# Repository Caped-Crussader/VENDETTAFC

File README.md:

# VENDETTA FPV Stack

> A fully open-source, custom-designed 4-in-1 ESC and F7 Flight Controller stack for FPV multirotors, designed from scratch in KiCad.

---

## Overview

The VENDETTA stack consists of two boards designed to work together as a matched pair, built around modern components and open firmware with no proprietary dependencies.

| Board | Folder | Status |
|---|---|---|
| VENDETTA ESC (VESC) | `/VESC` | Schematic complete, layout WIP |
| VENDETTA FC (VFC) | `/VFC` | Schematic complete, layout WIP |

---

## VENDETTA ESC (VESC)

A 30×30mm 4-in-1 ESC (25A x 4) designed for 3–6S FPV multirotors.

> Note: 6 Layer Board, GND (plane 2 and 5) plane photos not included.

### Specifications

| Parameter | Value |
|---|---|
| MCU | Artery AT32F421GBU7 |
| Gate Driver | NSG2065Q |
| MOSFETs | SP40N03GNJ (×6 per channel, 24 total) |
| Continuous current | 25A per channel |
| Burst current | 30A per channel |
| Input voltage | 3–6S LiPo (12.6V–25.2V) |
| Motor outputs | 4× 3-phase BLDC |
| Firmware | AM32 |
| Protocols | DShot150 / DShot300 / DShot600 |
| Telemetry | Bidirectional DShot (RPM) |
| Current sensing | INA185 + 0.5mΩ Kelvin shunt |
| TVS protection | SMBJ30A |
| Bulk capacitance | 320µF (32× 10µF MLCC) |
| BEC (8V) | MP9943GQ-Z |
| BEC (3.3V) | TLV76733 |
| Mounting | 30×30mm M3 |
| Connector | JST SH 1.0mm 8-pin (SM08B-SRSS-TB) |

### ESC Block Diagram

```
LiPo ──→ TVS + Bulk Caps ──→ 4× Half-Bridge (NSG2065Q + SP40N03GNJ)
                           ──→ 8V BEC ──→ Gate Driver VCC
                           ──→ Shunt (0.5mΩ Kelvin) ──→ INA185 ──→ AT32F421
AT32F421 ──→ DShot (from FC) ──→ PWM generation ──→ NSG2065Q ──→ Motors
```

---

## VENDETTA FC (VFC)

A 30×30mm F7 Flight Controller targeting feature parity with commercial boards like the SpeedyBee F7 V3, with improvements in IMU performance and power isolation.

> Note: 6 Layer Board, GND (plane 2 and 5) plane photos not included.

### Specifications

| Parameter | Value |
|---|---|
| MCU | STM32F722RETx (216MHz Cortex-M4) |
| IMU | ICM-42688-P (32kHz gyro, SPI) |
| Barometer | BMP388 (I2C) |
| Blackbox | W25N04KVZEIR (512MB NAND Flash, SPI) |
| Wireless | ESP32-C3 (WiFi + BT via UART1) |
| OSD | None (digital OSD via MSP DisplayPort) |
| Firmware | Betaflight |
| Motor outputs | 4× DShot (TIM2 CH1–CH4, PA0–PA3) |
| UARTs | 6× (UART3 OSD, UART4 DJI RX, UART5 ELRS, UART6 GPS, UART7 spare) |
| I2C | 1× (GPS compass) |
| USB | USB-C (USB 2.0 FS) |
| BEC (9V/2A) | MP9943GQ-Z |
| BEC (5V/3A) | MP9943GQ-Z |
| LDO Digital (3.3V/1A) | AP7361C |
| LDO Analog (3.3V/700mA) | NCP167AMX330 |
| Blackbox | 512MB onboard flash |
| DJI support | Air Unit / O3 via UART3+UART4 |
| GPS | UART7 + I2C (compass) |
| Receiver | UART5 (ELRS/CRSF/SBUS) |
| LED outputs | 4× |
| Buzzer | MOSFET driven |
| Mounting | 30×30mm M3 |

### FC Block Diagram

```
                    ┌─────────────────────────────┐
LiPo (via ESC) ────→│ 9V BEC → 5V BEC → 3.3V x2  │
                    │                             │
                    │  STM32F722 ←─SPI─→ ICM-42688-P (IMU)
                    │             ←─SPI─→ W25N04KV (Flash)
                    │             ←─UART1─→ ESP32-C3 (WiFi/BT)
                    │             ←─I2C─→ BMP388 (Baro)
                    │             ←─USB─→ USB-C
                    │             ──UART3/4──→ DJI Air Unit
                    │             ──UART5────→ Receiver (ELRS)
                    │             ──UART6────→ GPS
                    │             ──TIM2─────→ ESC DShot M1-M4
                    └─────────────────────────────┘
```

### Power Architecture

```
VBAT (from ESC 8-pin) ──→ 9V/2A (MP9943) ──→ DJI Air Unit
                                           ──→ 5V/3A (MP9943) ──→ JST 5V outputs
                                                               ──→ 3.3V Digital (AP7361C) ──→ STM32, ESP32, Flash
                                                               ──→ [Ferrite] ──→ 3.3V Analog (NCP167) ──→ IMU, Baro, VDDA
```

---

## Connector Pinout

### ESC → FC (JST SH 1.0mm 8-pin)

| Pin | Signal | Description |
|---|---|---|
| 1 | VBAT | Battery voltage |
| 2 | GND | Ground |
| 3 | M1 | Motor 1 DShot |
| 4 | M2 | Motor 2 DShot |
| 5 | M3 | Motor 3 DShot |
| 6 | M4 | Motor 4 DShot |
| 7 | CURR | Current sense (INA185 output) |
| 8 | TLM | ESC telemetry UART |

### FC Bottom Connectors (JST SH 1.0mm)

| Connector | Pins | Function |
|---|---|---|
| ESC | 8 | M1–M4, CURR, TLM, VBAT, GND |
| RECEIVER | 4 | +5V, GND, UART5_RX, UART5_TX |
| GPS | 6 | +5V, GND, UART6_TX, UART6_RX, SDA, SCL |
| DJI AIR UNIT | 6 | +9V, GND, UART3_TX, UART3_RX, UART4_RX, NC |
| UART5 | 4 | +5V, GND, TX, RX |
| LED 1–4 | 3 each | +5V, GND, Signal |
| BUZZER | 2 | +5V, Signal |

---

## Firmware (Not yet Completed)

### ESC — AM32

AM32 is the only supported firmware for the AT32F421 MCU.

Flash via DShot passthrough from Betaflight:
```
Betaflight Configurator → Motors → ESC Configuration → Flash All
```

Or via SWD using the exposed test pads (SWDIO/SWDCLK).

Recommended target: `AT32F421_VESC` — confirm correct pin mapping before flashing.

### FC — Betaflight

Target: `STM32F7X2` unified target or a custom target for this board.

Flash via USB DFU:
1. Hold BOOT button, plug USB-C
2. Open Betaflight Configurator → Firmware Flasher
3. Select STM32F7X2, flash

Or wirelessly via ESP32-C3 over WiFi through the SpeedyBee App.

---

## Repository Structure

```
VENDETTAFC/
├── VESC/
│   ├── VESC.kicad_pro
│   ├── VESC.kicad_sch
│   ├── ESC1.kicad_sch        # Per-channel ESC subsheet
│   └── ...
├── VFC/
│   ├── VENDETTAFC.kicad_pro
│   ├── VENDETTAFC.kicad_sch  # Top-level schematic
│   ├── interface.kicad_sch   # Connectors and I/O
│   ├── pwr.kicad_sch         # Power management
│   ├── sensor.kicad_sch      # IMU, baro, flash, ESP32
│   └── ...
└── README.md
```

---

## Design Files

Both boards are designed in **KiCad 10**. All schematic symbols and footprints use standard KiCad libraries plus LCSC-sourced footprints where needed.

To open:
```
KiCad 10 → Open Project → select .kicad_pro file
```

---

## Status

- [x] ESC schematic complete
- [x] FC schematic complete  
- [x] ESC PCB layout
- [x] FC PCB layout
- [x] Gerber generation
- [ ] First prototype order
- [ ] Firmware bringup
- [ ] Testing and validation

---

## License

Hardware design files are released under the **CERN Open Hardware Licence Version 2 - Strongly Reciprocal (CERN-OHL-S v2)**.

You are free to study, modify, distribute, and manufacture this hardware, provided derivatives are released under the same license with attribution.

---

## Author

Designed by **Caped-Crussader**

> Contributions, bug reports, and suggestions welcome via Issues.

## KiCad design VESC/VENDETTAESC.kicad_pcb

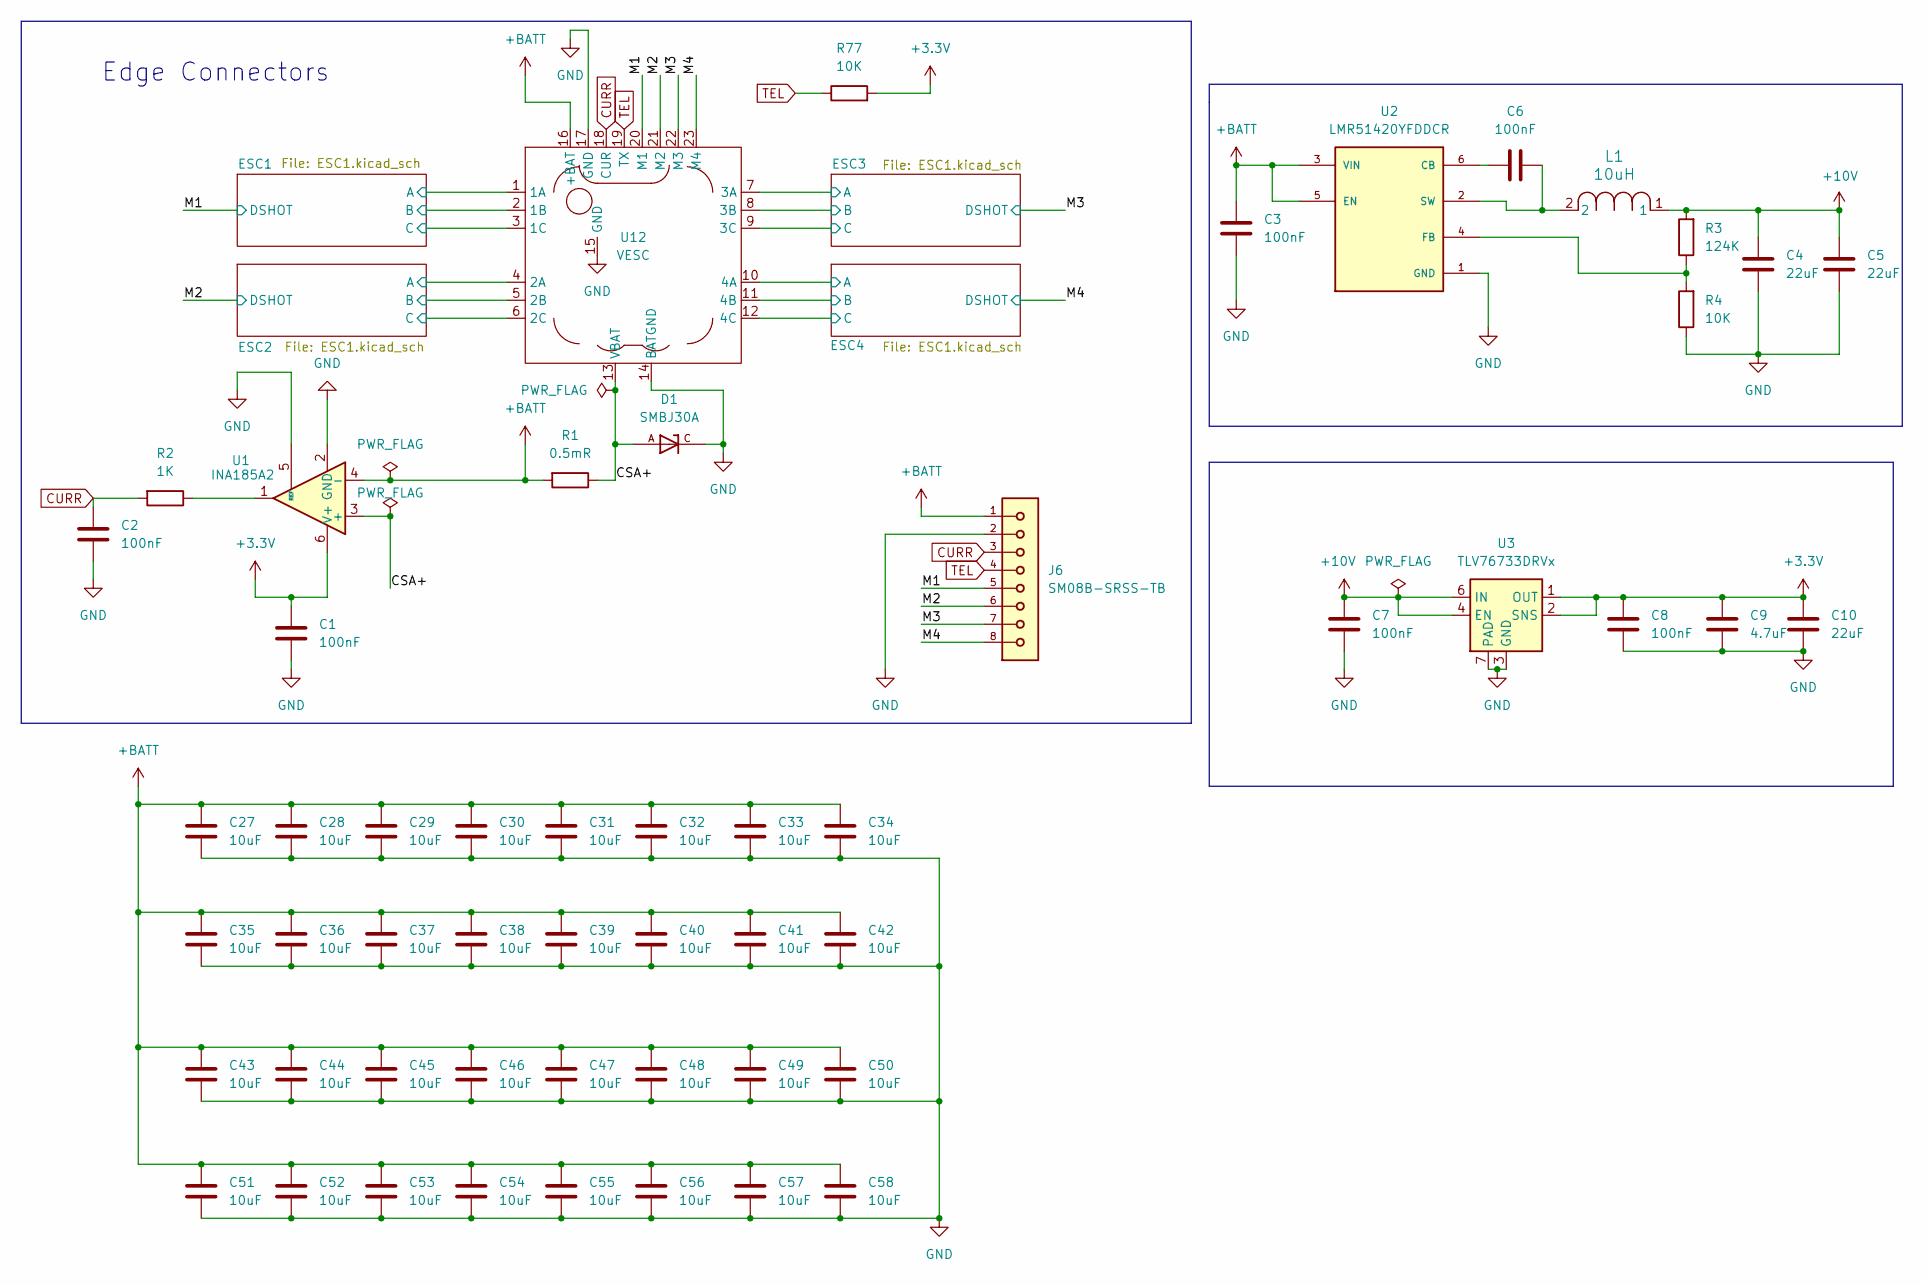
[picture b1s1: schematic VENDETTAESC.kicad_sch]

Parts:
C1, C2, C3, C6, C7, C8: 100nF; C_0402_1005Metric; Manufacturer Part Number GRM155R71H104KE14D; LCSC C77020
C4, C5, C10: 22uF; C_0805_2012Metric; Manufacturer Part Number CL21A226MAYNNNE; LCSC C602037
C9: 4.7uF; C_0603_1608Metric; Manufacturer Part Number CL10A475KO8NNNC; LCSC C19666
C27, C28, C29, C30, C31, C32, C33, C34, C35, C36, C37, C38, C39, C40, C41, C42, C43, C44, C45, C46, C47, C48, C49, C50, C51, C52, C53, C54, C55, C56, C57, C58: 10uF; C_0805_2012Metric; Manufacturer Part Number CL21A106KBYQNNE; LCSC C2932476
D1: SMBJ30A; DIOM4336X265N; PARTREV F2102; LCSC C135065
J6: SM08B-SRSS-TB; JST_SH_SM08B-SRSS-TB_1x08-1MP_P1.00mm_Horizontal; Manufacturer Part Number SM08B-SRSS-TB(LF)(SN); LCSC C160407
L1: 10uH; L_Changjiang_FTC404020S; Manufacturer Part Number GXTC0420-100-MT; LCSC C53198553
R1: 0.5mR; R_2512_6332Metric; Manufacturer Part Number EBWM2512JL500S9; LCSC C19679480
R2: 1K; R_0402_1005Metric; Manufacturer Part Number RC0402FR-071KL; LCSC C106235
R3: 124K; R_0402_1005Metric; Manufacturer Part Number 0402WGF1243TCE; LCSC C36777
R4, R77: 10K; R_0402_1005Metric; Manufacturer Part Number RC0402JR-0710KL; LCSC C60489
U1: INA185A2; SOT-563; Manufacturer Part Number INA185A2IDRLR; LCSC C2059320
U2: LMR51420YFDDCR; SOT95P280X110-6N; PARTREV C; LCSC C7296200
U3: TLV76733DRVx; WSON-6-1EP_2x2mm_P0.65mm_EP1x1.6mm_ThermalVias; Manufacturer Part Number TLV76733DRVR; LCSC C2848334
U12: VESC

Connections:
+3.3V: C1.1, C8.1, C9.1, C10.1, R77.2, U1.6 (V+), U3.1 (OUT), U3.2 (SNS); also elsewhere on the board
+10V: C4.1, C5.1, C7.1, L1.1, R3.2, U3.4 (EN), U3.6 (IN); also elsewhere on the board
+BATT: C3.1, C27.1, C28.1, C29.1, C30.1, C31.1, C32.1, C33.1, C34.1, C35.1, C36.1, C37.1, C38.1, C39.1, C40.1, C41.1, C42.1, C43.1, C44.1, C45.1, C46.1, C47.1, C48.1, C49.1, C50.1, C51.1, C52.1, C53.1, C54.1, C55.1, C56.1, C57.1, C58.1, J6.1, R1.2, U1.4 (-), U2.3 (VIN), U2.5 (EN), U12.16 (+BAT); also elsewhere on the board
/CSA+: D1.A, R1.1, U1.3 (+), U12.13 (VBAT)
/ESC1/MOTORA: U12.1 (1A); also elsewhere on the board
/ESC1/MOTORB: U12.2 (1B); also elsewhere on the board
/ESC1/MOTORC: U12.3 (1C); also elsewhere on the board
/ESC2/MOTORA: U12.4 (2A); also elsewhere on the board
/ESC2/MOTORB: U12.5 (2B); also elsewhere on the board
/ESC2/MOTORC: U12.6 (2C); also elsewhere on the board
/ESC3/MOTORA: U12.7 (3A); also elsewhere on the board
/ESC3/MOTORB: U12.8 (3B); also elsewhere on the board
/ESC3/MOTORC: U12.9 (3C); also elsewhere on the board
/ESC4/MOTORA: U12.10 (4A); also elsewhere on the board
/ESC4/MOTORB: U12.11 (4B); also elsewhere on the board
/ESC4/MOTORC: U12.12 (4C); also elsewhere on the board
/M1: J6.5, U12.20 (M1); also elsewhere on the board
/M2: J6.6, U12.21 (M2); also elsewhere on the board
/M3: J6.7, U12.22 (M3); also elsewhere on the board
/M4: J6.8, U12.23 (M4); also elsewhere on the board
CURR: C2.1, J6.3, R2.2, U12.18 (CUR)
GND: C1.2, C2.2, C3.2, C4.2, C5.2, C7.2, C8.2, C9.2, C10.2, C27.2, C28.2, C29.2, C30.2, C31.2, C32.2, C33.2, C34.2, C35.2, C36.2, C37.2, C38.2, C39.2, C40.2, C41.2, C42.2, C43.2, C44.2, C45.2, C46.2, C47.2, C48.2, C49.2, C50.2, C51.2, C52.2, C53.2, C54.2, C55.2, C56.2, C57.2, C58.2, D1.C, J6.2, R4.1, U1.2 (GND), U1.5 (REF), U2.1 (GND), U3.3 (GND), U3.5 (GND), U3.7 (PAD), U12.14 (BATGND), U12.15 (GND), U12.17 (GND); also elsewhere on the board
unnamed: R2.1, U1.1
unnamed: C6.2, U2.6 (CB)
unnamed: R3.1, R4.2, U2.4 (FB)
unnamed: C6.1, L1.2, U2.2 (SW)
TEL: J6.4, R77.1, U12.19 (TX); also elsewhere on the board

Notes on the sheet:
Edge Connectors

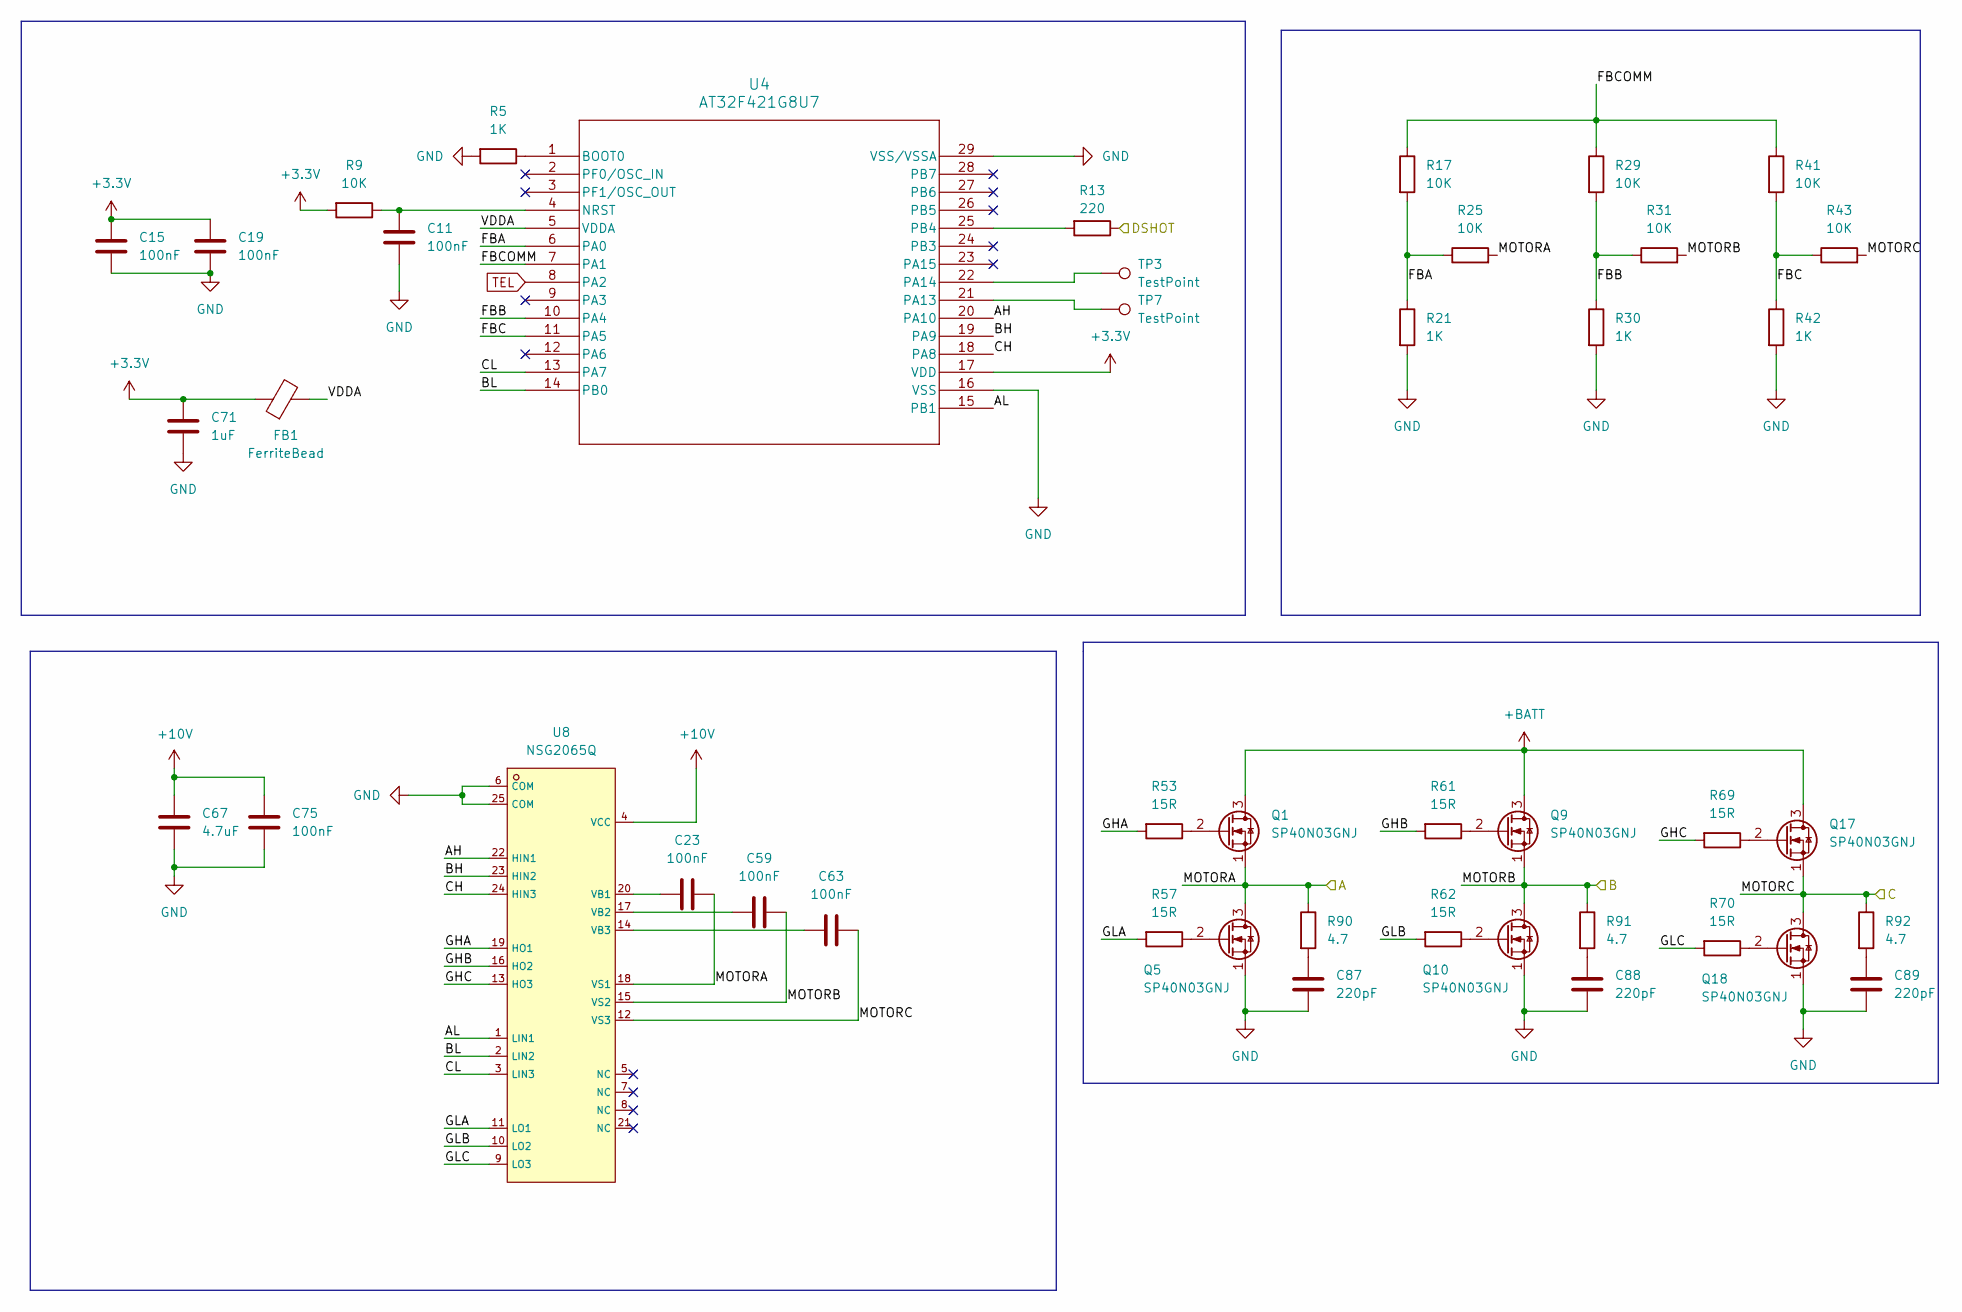
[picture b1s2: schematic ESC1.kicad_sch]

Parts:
C11, C15, C19, C23, C59, C63, C75: 100nF; C_0402_1005Metric; Manufacturer Part Number GRM155R71H104KE14D; LCSC C77020
C67: 4.7uF; C_0603_1608Metric; Manufacturer Part Number CL10A475KO8NNNC; LCSC C19666
C71: 1uF; C_0402_1005Metric; Manufacturer Part Number CL05A105KO5NNNC; LCSC C29266
C87, C88, C89: 220pF; C_0402_1005Metric; Manufacturer Part Number AC0402KRX7R0BB221; LCSC C7209937
FB1: FerriteBead; L_0402_1005Metric; Manufacturer Part Number CBW100505U101T; LCSC C124089
Q1, Q5, Q9, Q10, Q17, Q18: SP40N03GNJ; POWERPAK-1212-8_L3.0-W3.0-P0.65-LS3.3-BL; Manufacturer Part Number SP40N03GNJ; LCSC C22466709
R5, R21, R30, R42: 1K; R_0402_1005Metric; Manufacturer Part Number RC0402FR-071KL; LCSC C106235
R9, R17, R25, R29, R31, R41, R43: 10K; R_0402_1005Metric; Manufacturer Part Number RC0402JR-0710KL; LCSC C60489
R13: 220; R_0402_1005Metric; Manufacturer Part Number 0402WGJ0220TCE; LCSC C25152
R53, R57, R61, R62, R69, R70: 15R; R_0402_1005Metric; Manufacturer Part Number 0402WGF150JTCE; LCSC C25083
R90, R91, R92: 4.7; R_0402_1005Metric; Manufacturer Part Number 0402WGJ047JTCE; LCSC C25169
TP3, TP7: TestPoint; TestPoint_Pad_D1.0mm
U4: AT32F421G8U7; QFN28_4x4_ART; Manufacturer Part Number AT32F421G8U7; LCSC C2765098
U8: NSG2065Q; QFN-24_L4.0-W4.0-P0.50-TL-EP2.8; Manufacturer Part Number NSG2065Q; LCSC C41414478

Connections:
+3.3V: C15.1, C19.1, C71.1, FB1.1, R9.2, U4.17 (VDD); also elsewhere on the board
+10V: C67.1, C75.1, U8.4 (VCC); also elsewhere on the board
+BATT: Q1.3 (D), Q9.3 (D), Q17.3 (D); also elsewhere on the board
/ESC1/AH: U4.20 (PA10), U8.22 (HIN1)
/ESC1/AL: U4.15 (PB1), U8.1 (LIN1)
/ESC1/BH: U4.19 (PA9), U8.23 (HIN2)
/ESC1/BL: U4.14 (PB0), U8.2 (LIN2)
/ESC1/CH: U4.18 (PA8), U8.24 (HIN3)
/ESC1/CL: U4.13 (PA7), U8.3 (LIN3)
/ESC1/FBA: R17.2, R21.1, R25.1, U4.6 (PA0)
/ESC1/FBB: R29.2, R30.1, R31.1, U4.10 (PA4)
/ESC1/FBC: R41.2, R42.1, R43.1, U4.11 (PA5)
/ESC1/FBCOMM: R17.1, R29.1, R41.1, U4.7 (PA1)
/ESC1/GHA: R53.2, U8.19 (HO1)
/ESC1/GHB: R61.2, U8.16 (HO2)
/ESC1/GHC: R69.2, U8.13 (HO3)
/ESC1/GLA: R57.2, U8.11 (LO1)
/ESC1/GLB: R62.2, U8.10 (LO2)
/ESC1/GLC: R70.2, U8.9 (LO3)
/ESC1/MOTORA: C23.1, Q1.1 (S), Q5.3 (D), R25.2, R90.1, U8.18 (VS1); also elsewhere on the board
/ESC1/MOTORB: C59.1, Q9.1 (S), Q10.3 (D), R31.2, R91.1, U8.15 (VS2); also elsewhere on the board
/ESC1/MOTORC: C63.1, Q17.1 (S), Q18.3 (D), R43.2, R92.1, U8.12 (VS3); also elsewhere on the board
/ESC1/VDDA: FB1.2, U4.5 (VDDA)
/M1: R13.1; also elsewhere on the board
GND: C11.2, C15.2, C19.2, C67.2, C71.2, C75.2, C87.2, C88.2, C89.2, Q5.1 (S), Q10.1 (S), Q18.1 (S), R5.2, R21.2, R30.2, R42.2, U4.16 (VSS), U4.29 (VSS/VSSA), U8.6 (COM), U8.25 (COM); also elsewhere on the board
unnamed: C87.1, R90.2
unnamed: C88.1, R91.2
unnamed: C89.1, R92.2
unnamed: Q1.2 (G), R53.1
unnamed: Q5.2 (G), R57.1
unnamed: Q9.2 (G), R61.1
unnamed: Q10.2 (G), R62.1
unnamed: Q17.2 (G), R69.1
unnamed: Q18.2 (G), R70.1
unnamed: R5.1, U4.1 (BOOT0)
unnamed: C11.1, R9.1, U4.4 (NRST)
unnamed: TP7.1 (1_1), U4.21 (PA13)
unnamed: TP3.1 (1_1), U4.22 (PA14)
unnamed: R13.2, U4.25 (PB4)
unnamed: C23.2, U8.20 (VB1)
unnamed: C59.2, U8.17 (VB2)
unnamed: C63.2, U8.14 (VB3)
TEL: U4.8 (PA2); also elsewhere on the board

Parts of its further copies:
C12, C13, C14, C16, C17, C18, C20, C21, C22, C24, C25, C26, C60, C61, C62, C64, C65, C66, C76, C77, C78: 100nF; C_0402_1005Metric; Manufacturer Part Number GRM155R71H104KE14D; LCSC C77020
C68, C69, C70: 4.7uF; C_0603_1608Metric; Manufacturer Part Number CL10A475KO8NNNC; LCSC C19666
C72, C73, C74: 1uF; C_0402_1005Metric; Manufacturer Part Number CL05A105KO5NNNC; LCSC C29266
C90, C91, C92, C93, C94, C95, C96, C97, C98: 220pF; C_0402_1005Metric; Manufacturer Part Number AC0402KRX7R0BB221; LCSC C7209937
FB2, FB3, FB4: FerriteBead; L_0402_1005Metric; Manufacturer Part Number CBW100505U101T; LCSC C124089
Q2, Q3, Q4, Q6, Q7, Q8, Q11, Q12, Q13, Q14, Q15, Q16, Q19, Q20, Q21, Q22, Q23, Q24: SP40N03GNJ; POWERPAK-1212-8_L3.0-W3.0-P0.65-LS3.3-BL; Manufacturer Part Number SP40N03GNJ; LCSC C22466709
R6, R7, R8, R22, R23, R24, R33, R36, R39, R45, R48, R51: 1K; R_0402_1005Metric; Manufacturer Part Number RC0402FR-071KL; LCSC C106235
R10, R11, R12, R18, R19, R20, R26, R27, R28, R32, R34, R35, R37, R38, R40, R44, R46, R47, R49, R50, R52: 10K; R_0402_1005Metric; Manufacturer Part Number RC0402JR-0710KL; LCSC C60489
R14, R15, R16: 220; R_0402_1005Metric; Manufacturer Part Number 0402WGJ0220TCE; LCSC C25152
R54, R55, R56, R58, R59, R60, R63, R64, R65, R66, R67, R68, R71, R72, R73, R74, R75, R76: 15R; R_0402_1005Metric; Manufacturer Part Number 0402WGF150JTCE; LCSC C25083
R93, R94, R95, R96, R97, R98, R99, R100, R101: 4.7; R_0402_1005Metric; Manufacturer Part Number 0402WGJ047JTCE; LCSC C25169
TP4, TP5, TP6, TP8, TP9, TP10: TestPoint; TestPoint_Pad_D1.0mm
U5, U6, U7: AT32F421G8U7; QFN28_4x4_ART; Manufacturer Part Number AT32F421G8U7; LCSC C2765098
U9, U10, U11: NSG2065Q; QFN-24_L4.0-W4.0-P0.50-TL-EP2.8; Manufacturer Part Number NSG2065Q; LCSC C41414478

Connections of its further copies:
+3.3V: C16.1, C17.1, C18.1, C20.1, C21.1, C22.1, C72.1, C73.1, C74.1, FB2.1, FB3.1, FB4.1, R10.2, R11.2, R12.2, U5.17 (VDD), U6.17 (VDD), U7.17 (VDD); also elsewhere on the board
+10V: C68.1, C69.1, C70.1, C76.1, C77.1, C78.1, U9.4 (VCC), U10.4 (VCC), U11.4 (VCC); also elsewhere on the board
+BATT: Q2.3 (D), Q3.3 (D), Q4.3 (D), Q11.3 (D), Q13.3 (D), Q15.3 (D), Q19.3 (D), Q21.3 (D), Q23.3 (D); also elsewhere on the board
/ESC2/AH: U5.20 (PA10), U9.22 (HIN1)
/ESC2/AL: U5.15 (PB1), U9.1 (LIN1)
/ESC2/BH: U5.19 (PA9), U9.23 (HIN2)
/ESC2/BL: U5.14 (PB0), U9.2 (LIN2)
/ESC2/CH: U5.18 (PA8), U9.24 (HIN3)
/ESC2/CL: U5.13 (PA7), U9.3 (LIN3)
/ESC2/FBA: R18.2, R22.1, R26.1, U5.6 (PA0)
/ESC2/FBB: R32.2, R33.1, R34.1, U5.10 (PA4)
/ESC2/FBC: R44.2, R45.1, R46.1, U5.11 (PA5)
/ESC2/FBCOMM: R18.1, R32.1, R44.1, U5.7 (PA1)
/ESC2/GHA: R54.2, U9.19 (HO1)
/ESC2/GHB: R63.2, U9.16 (HO2)
/ESC2/GHC: R71.2, U9.13 (HO3)
/ESC2/GLA: R58.2, U9.11 (LO1)
/ESC2/GLB: R64.2, U9.10 (LO2)
/ESC2/GLC: R72.2, U9.9 (LO3)
/ESC2/MOTORA: C24.1, Q2.1 (S), Q6.3 (D), R26.2, R93.1, U9.18 (VS1); also elsewhere on the board
/ESC2/MOTORB: C60.1, Q11.1 (S), Q12.3 (D), R34.2, R94.1, U9.15 (VS2); also elsewhere on the board
/ESC2/MOTORC: C64.1, Q19.1 (S), Q20.3 (D), R46.2, R95.1, U9.12 (VS3); also elsewhere on the board
/ESC2/VDDA: FB2.2, U5.5 (VDDA)
/ESC3/AH: U6.20 (PA10), U10.22 (HIN1)
/ESC3/AL: U6.15 (PB1), U10.1 (LIN1)
/ESC3/BH: U6.19 (PA9), U10.23 (HIN2)
/ESC3/BL: U6.14 (PB0), U10.2 (LIN2)
/ESC3/CH: U6.18 (PA8), U10.24 (HIN3)
/ESC3/CL: U6.13 (PA7), U10.3 (LIN3)
/ESC3/FBA: R19.2, R23.1, R27.1, U6.6 (PA0)
/ESC3/FBB: R35.2, R36.1, R37.1, U6.10 (PA4)
/ESC3/FBC: R47.2, R48.1, R49.1, U6.11 (PA5)
/ESC3/FBCOMM: R19.1, R35.1, R47.1, U6.7 (PA1)
/ESC3/GHA: R55.2, U10.19 (HO1)
/ESC3/GHB: R65.2, U10.16 (HO2)
/ESC3/GHC: R73.2, U10.13 (HO3)
/ESC3/GLA: R59.2, U10.11 (LO1)
/ESC3/GLB: R66.2, U10.10 (LO2)
/ESC3/GLC: R74.2, U10.9 (LO3)
/ESC3/MOTORA: C25.1, Q3.1 (S), Q7.3 (D), R27.2, R96.1, U10.18 (VS1); also elsewhere on the board
/ESC3/MOTORB: C61.1, Q13.1 (S), Q14.3 (D), R37.2, R97.1, U10.15 (VS2); also elsewhere on the board
/ESC3/MOTORC: C65.1, Q21.1 (S), Q22.3 (D), R49.2, R98.1, U10.12 (VS3); also elsewhere on the board
/ESC3/VDDA: FB3.2, U6.5 (VDDA)
/ESC4/AH: U7.20 (PA10), U11.22 (HIN1)
/ESC4/AL: U7.15 (PB1), U11.1 (LIN1)
/ESC4/BH: U7.19 (PA9), U11.23 (HIN2)
/ESC4/BL: U7.14 (PB0), U11.2 (LIN2)
/ESC4/CH: U7.18 (PA8), U11.24 (HIN3)
/ESC4/CL: U7.13 (PA7), U11.3 (LIN3)
/ESC4/FBA: R20.2, R24.1, R28.1, U7.6 (PA0)
/ESC4/FBB: R38.2, R39.1, R40.1, U7.10 (PA4)
/ESC4/FBC: R50.2, R51.1, R52.1, U7.11 (PA5)
/ESC4/FBCOMM: R20.1, R38.1, R50.1, U7.7 (PA1)
/ESC4/GHA: R56.2, U11.19 (HO1)
/ESC4/GHB: R67.2, U11.16 (HO2)
/ESC4/GHC: R75.2, U11.13 (HO3)
/ESC4/GLA: R60.2, U11.11 (LO1)
/ESC4/GLB: R68.2, U11.10 (LO2)
/ESC4/GLC: R76.2, U11.9 (LO3)
/ESC4/MOTORA: C26.1, Q4.1 (S), Q8.3 (D), R28.2, R99.1, U11.18 (VS1); also elsewhere on the board
/ESC4/MOTORB: C62.1, Q15.1 (S), Q16.3 (D), R40.2, R100.1, U11.15 (VS2); also elsewhere on the board
/ESC4/MOTORC: C66.1, Q23.1 (S), Q24.3 (D), R52.2, R101.1, U11.12 (VS3); also elsewhere on the board
/ESC4/VDDA: FB4.2, U7.5 (VDDA)
/M2: R14.1; also elsewhere on the board
/M3: R15.1; also elsewhere on the board
/M4: R16.1; also elsewhere on the board
GND: C12.2, C13.2, C14.2, C16.2, C17.2, C18.2, C20.2, C21.2, C22.2, C68.2, C69.2, C70.2, C72.2, C73.2, C74.2, C76.2, C77.2, C78.2, C90.2, C91.2, C92.2, C93.2, C94.2, C95.2, C96.2, C97.2, C98.2, Q6.1 (S), Q7.1 (S), Q8.1 (S), Q12.1 (S), Q14.1 (S), Q16.1 (S), Q20.1 (S), Q22.1 (S), Q24.1 (S), R6.2, R7.2, R8.2, R22.2, R23.2, R24.2, R33.2, R36.2, R39.2, R45.2, R48.2, R51.2, U5.16 (VSS), U5.29 (VSS/VSSA), U6.16 (VSS), U6.29 (VSS/VSSA), U7.16 (VSS), U7.29 (VSS/VSSA), U9.6 (COM), U9.25 (COM), U10.6 (COM), U10.25 (COM), U11.6 (COM), U11.25 (COM); also elsewhere on the board
unnamed: C90.1, R93.2
unnamed: C91.1, R94.2
unnamed: C92.1, R95.2
unnamed: C93.1, R96.2
unnamed: C94.1, R97.2
unnamed: C95.1, R98.2
unnamed: C96.1, R99.2
unnamed: C97.1, R100.2
unnamed: C98.1, R101.2
unnamed: Q2.2 (G), R54.1
unnamed: Q3.2 (G), R55.1
unnamed: Q4.2 (G), R56.1
unnamed: Q6.2 (G), R58.1
unnamed: Q7.2 (G), R59.1
unnamed: Q8.2 (G), R60.1
unnamed: Q11.2 (G), R63.1
unnamed: Q12.2 (G), R64.1
unnamed: Q13.2 (G), R65.1
unnamed: Q14.2 (G), R66.1
unnamed: Q15.2 (G), R67.1
unnamed: Q16.2 (G), R68.1
unnamed: Q19.2 (G), R71.1
unnamed: Q20.2 (G), R72.1
unnamed: Q21.2 (G), R73.1
unnamed: Q22.2 (G), R74.1
unnamed: Q23.2 (G), R75.1
unnamed: Q24.2 (G), R76.1
unnamed: R6.1, U5.1 (BOOT0)
unnamed: C12.1, R10.1, U5.4 (NRST)
unnamed: TP8.1 (1_1), U5.21 (PA13)
unnamed: TP4.1 (1_1), U5.22 (PA14)
unnamed: R14.2, U5.25 (PB4)
unnamed: R7.1, U6.1 (BOOT0)
unnamed: C13.1, R11.1, U6.4 (NRST)
unnamed: TP9.1 (1_1), U6.21 (PA13)
unnamed: TP5.1 (1_1), U6.22 (PA14)
unnamed: R15.2, U6.25 (PB4)
unnamed: R8.1, U7.1 (BOOT0)
unnamed: C14.1, R12.1, U7.4 (NRST)
unnamed: TP10.1 (1_1), U7.21 (PA13)
unnamed: TP6.1 (1_1), U7.22 (PA14)
unnamed: R16.2, U7.25 (PB4)
unnamed: C24.2, U9.20 (VB1)
unnamed: C60.2, U9.17 (VB2)
unnamed: C64.2, U9.14 (VB3)
unnamed: C25.2, U10.20 (VB1)
unnamed: C61.2, U10.17 (VB2)
unnamed: C65.2, U10.14 (VB3)
unnamed: C26.2, U11.20 (VB1)
unnamed: C62.2, U11.17 (VB2)
unnamed: C66.2, U11.14 (VB3)
TEL: U5.8 (PA2), U6.8 (PA2), U7.8 (PA2); also elsewhere on the board

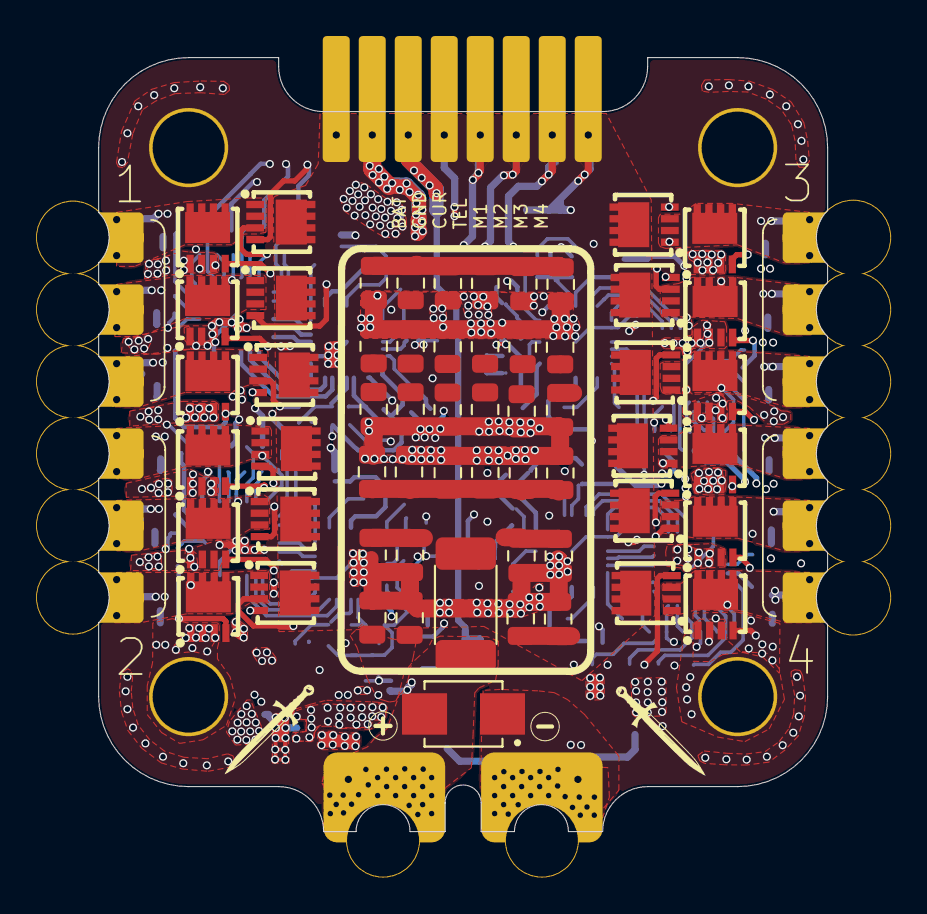
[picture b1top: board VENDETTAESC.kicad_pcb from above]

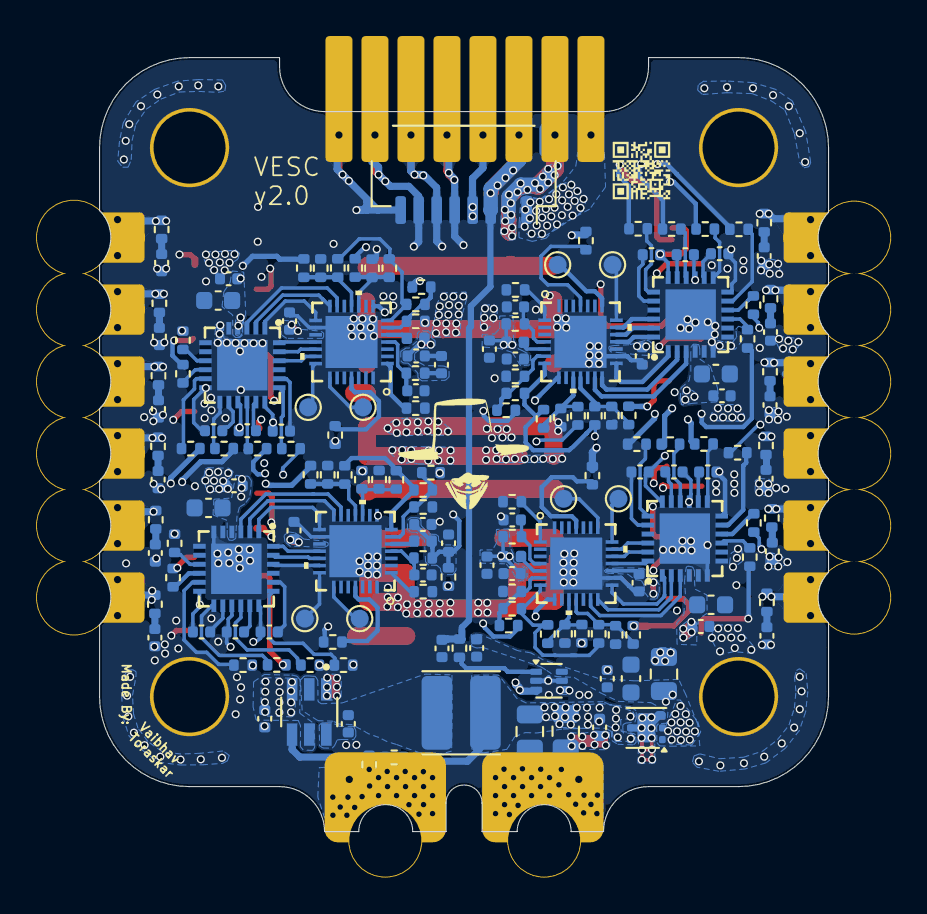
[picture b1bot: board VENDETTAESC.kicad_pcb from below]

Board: 6 copper layers, 40.5 x 43.0 mm, 235 parts (172 on the bottom side), 163 nets.

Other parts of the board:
knifelogo1, knifelogo2: LOGO; KNIFE_F
minus: LOGO; minus_f
plus: LOGO; plus_f
vlogo: LOGO; VLOGO

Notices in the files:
README.md:
License: CERN-OHL-S
VESC/ESC1.kicad_sch:
Copyright (C) 2026 Caped-Crussader
Licensed under CERN-OHL-S v2
